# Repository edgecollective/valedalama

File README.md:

# valedalama

https://github.com/the-louie/arduino-lmic/tree/louie-add-naive-eu433-support

bossac -p /dev/cu.usbmodem14301 -e -w -v -R adafruit-circuitpython-boardname-version.bin

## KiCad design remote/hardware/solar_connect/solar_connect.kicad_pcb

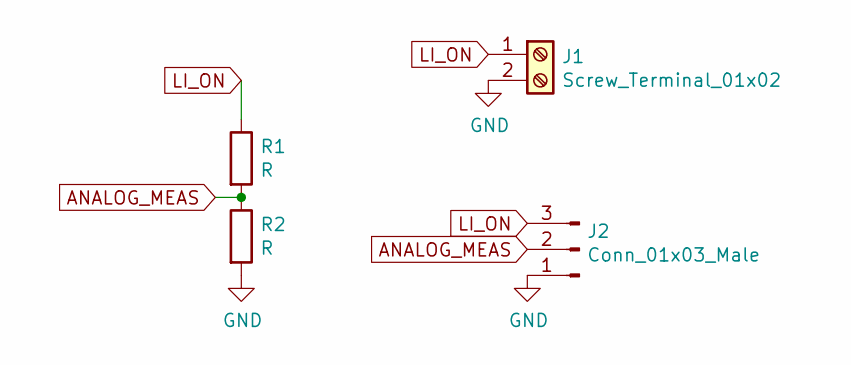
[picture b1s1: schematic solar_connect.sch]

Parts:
J1: Screw_Terminal_01x02; TerminalBlock_Phoenix_PT-1,5-2-3.5-H_1x02_P3.50mm_Horizontal
J2: Conn_01x03_Male; PinHeader_1x03_P2.54mm_Vertical
R1, R2: R; R_Axial_DIN0309_L9.0mm_D3.2mm_P2.54mm_Vertical

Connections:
ANALOG_MEAS: J2.2, R1.2, R2.1
GND: J1.2, J2.1, R2.2
LI_ON: J1.1, J2.3, R1.1

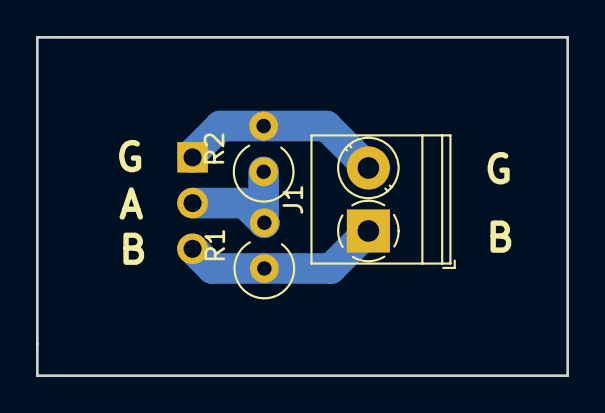
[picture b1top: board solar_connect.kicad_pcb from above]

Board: 2 copper layers, 29.5 x 18.8 mm, 4 parts (1 on the bottom side), 3 nets.

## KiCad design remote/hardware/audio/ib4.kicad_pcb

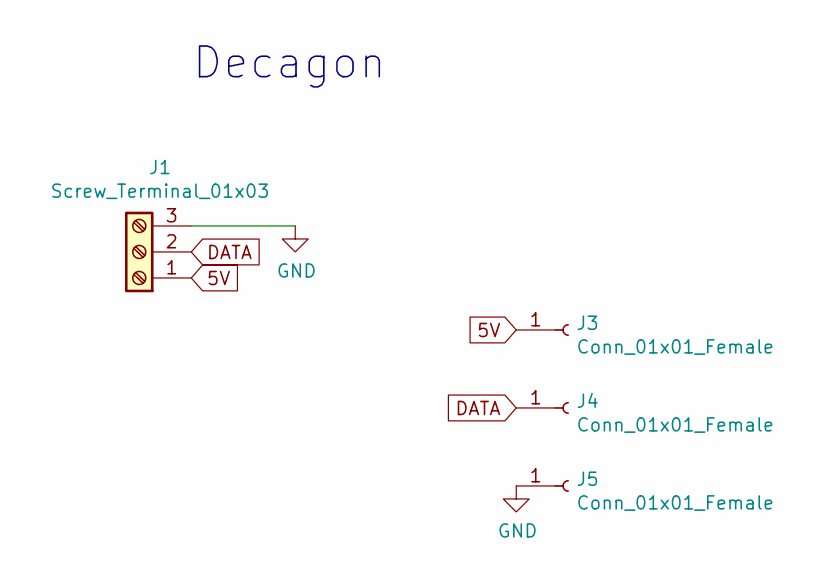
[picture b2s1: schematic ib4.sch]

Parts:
J1: Screw_Terminal_01x03; TerminalBlock_Phoenix_PT-1,5-3-3.5-H_1x03_P3.50mm_Horizontal
J3, J4, J5: Conn_01x01_Female; PinSocket_1x01_P2.54mm_Vertical

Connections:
5V: J1.1, J3.1
DATA: J1.2, J4.1
GND: J1.3, J5.1

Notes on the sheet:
Decagon

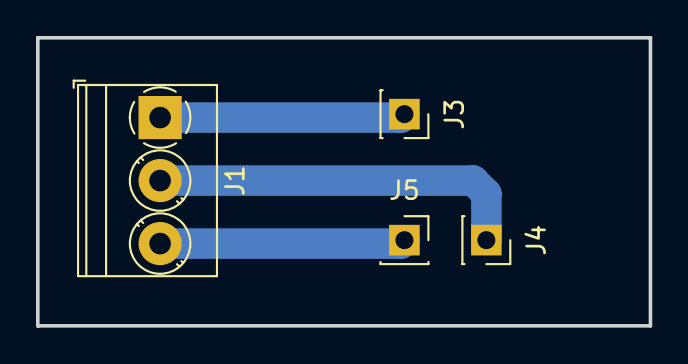
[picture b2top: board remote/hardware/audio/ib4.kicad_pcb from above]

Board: 4 copper layers, 34.0 x 16.0 mm, 4 parts (0 on the bottom side), 3 nets.

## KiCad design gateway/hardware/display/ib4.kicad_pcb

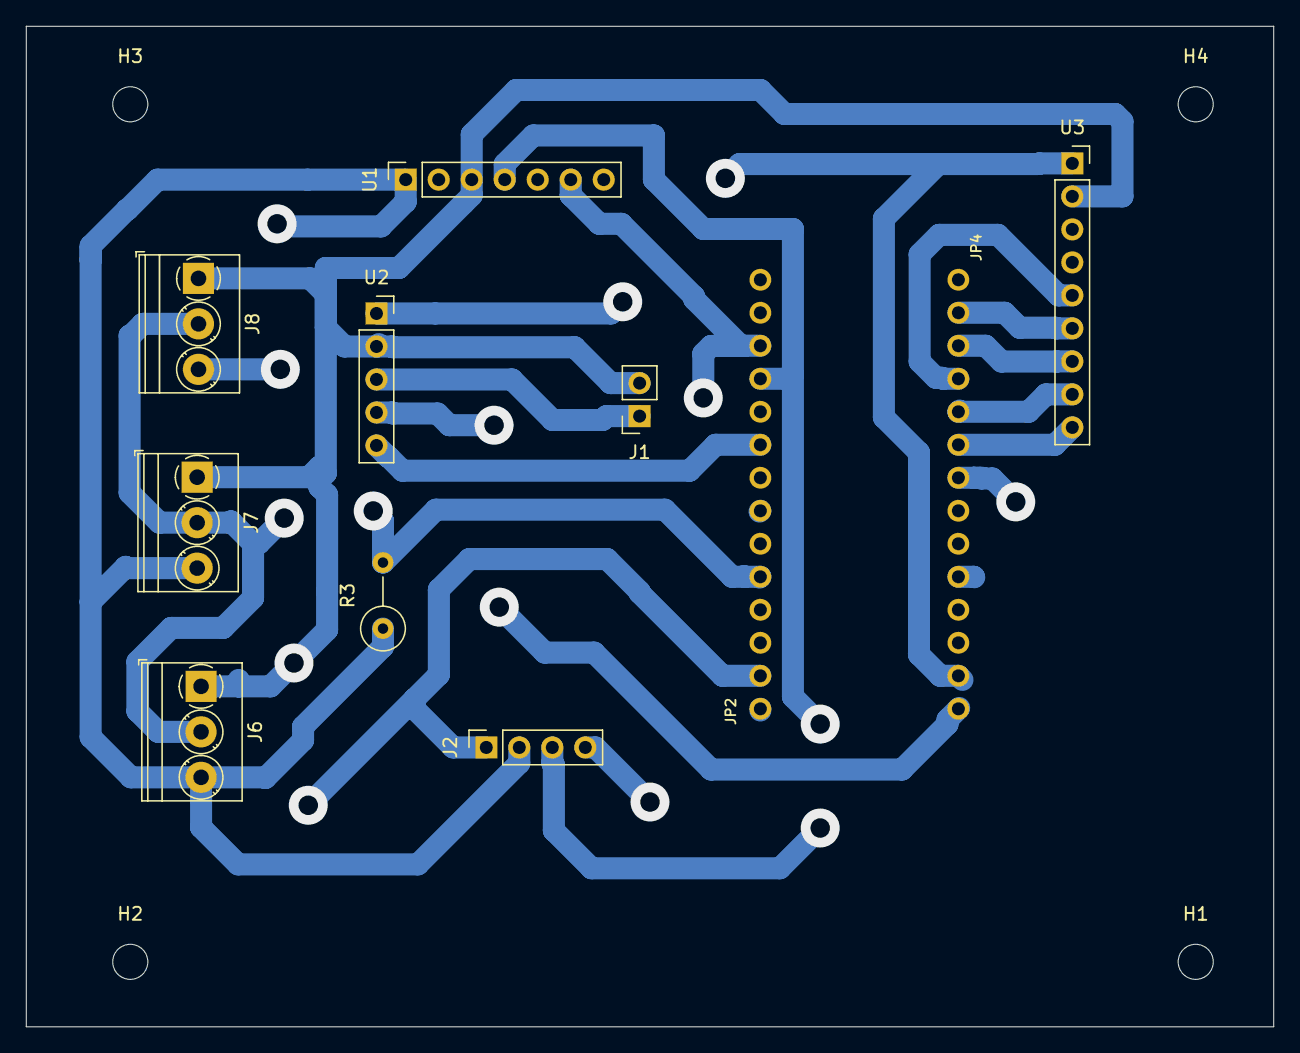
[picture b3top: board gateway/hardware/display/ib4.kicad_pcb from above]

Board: 4 copper layers, 96.0 x 77.0 mm, 15 parts (0 on the bottom side), 12 nets.

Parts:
H1, H2, H3, H4: MountingHole; MountingHole_2.7mm_M2.5
J1: Conn_01x02_Female; PinSocket_1x02_P2.54mm_Vertical
J2: Conn_01x04_Female; PinSocket_1x04_P2.54mm_Vertical
J6, J7, J8: Screw_Terminal_01x03; TerminalBlock_Phoenix_PT-1,5-3-3.5-H_1x03_P3.50mm_Horizontal
JP2, JP4: HEADER-1X14; 1X14_ROUND70
R3: R; R_Axial_DIN0309_L9.0mm_D3.2mm_P5.08mm_Vertical
U1: bme280; PinSocket_1x07_P2.54mm_Vertical
U2: tpl5110; PinSocket_1x05_P2.54mm_Vertical
U3: lora_breakout; PinSocket_1x09_P2.54mm_Vertical

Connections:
+3V3: J2.2, J6.3, J7.3, J8.3, JP4.13, R3.1, U1.1, U2.1, U3.1
D12: J6.2, J7.2, J8.2, JP2.5, R3.2
GND: J1.2, J2.1, J6.1, J7.1, J8.1, JP2.2, U1.3, U2.2, U3.2
LORA_CS: JP4.5, U3.8
LORA_RST: JP4.6, U3.9
MISO: JP4.2, U3.6
MOSI: JP4.3, U3.7
unnamed: J1.1, U2.3
SCK: JP4.4, U3.5
SCL: J2.3, JP2.11, U1.4
SDA: J2.4, JP2.12, U1.6
TIMER: JP4.14, U2.4

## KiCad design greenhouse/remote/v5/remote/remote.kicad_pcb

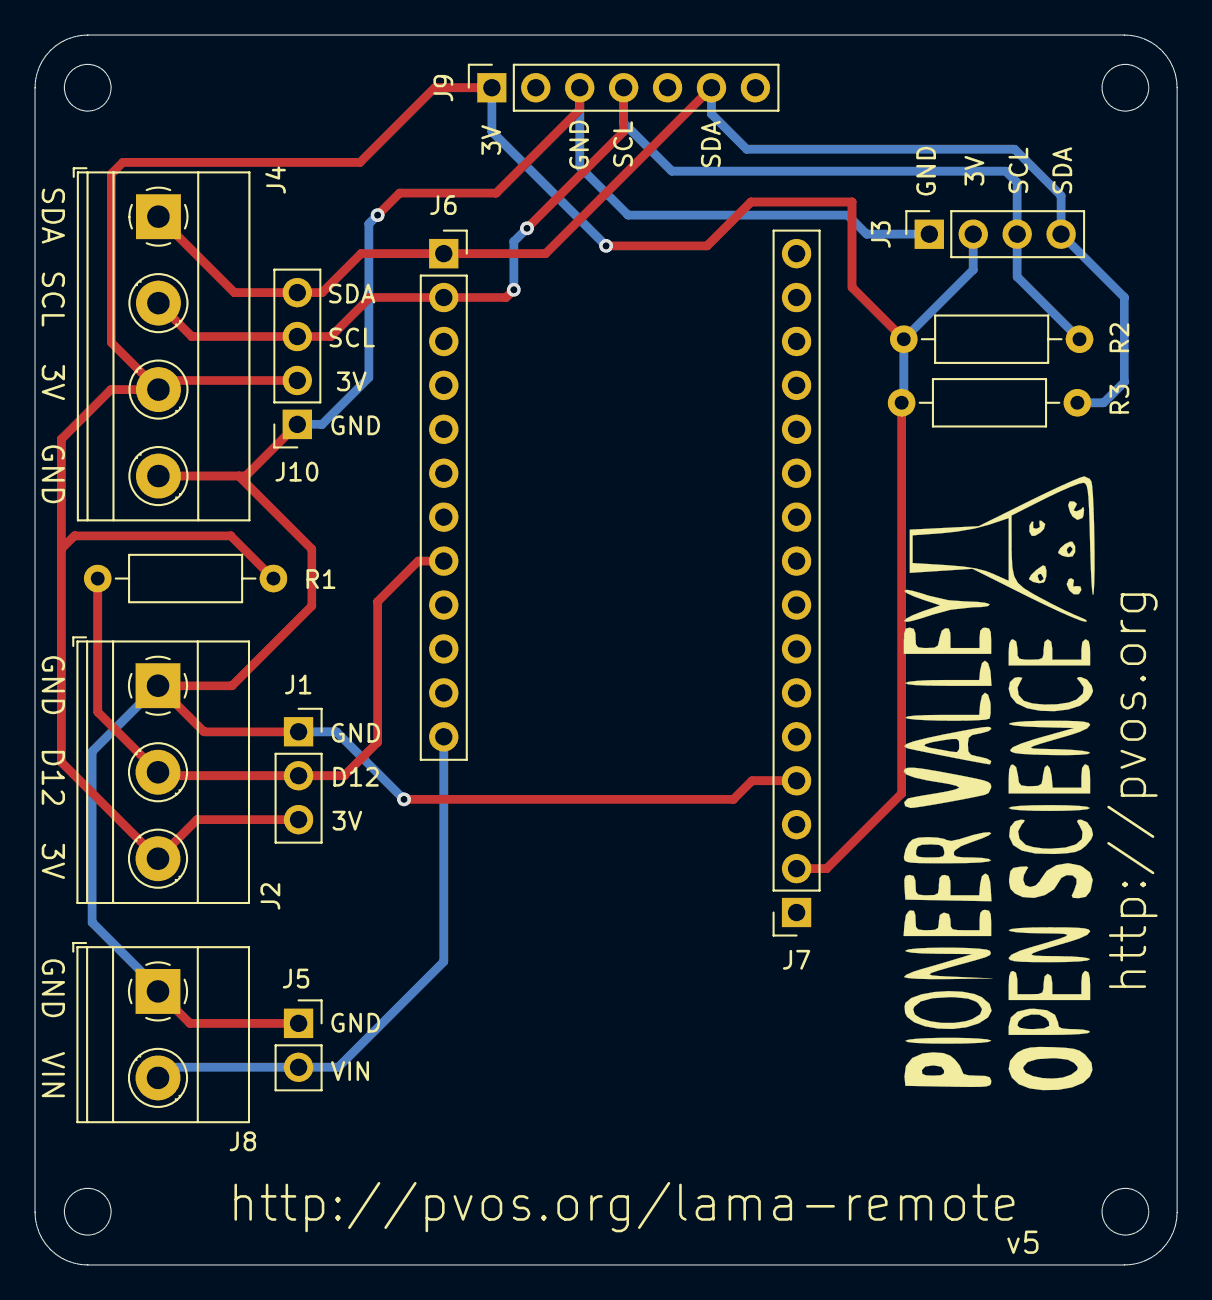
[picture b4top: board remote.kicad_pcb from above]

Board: 2 copper layers, 66.0 x 71.1 mm, 17 parts (0 on the bottom side), 6 nets.

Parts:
H1, H2, H3, H4: MountingHole; MountingHole_2.7mm_M2.5
J1: Conn_01x03_Female; PinSocket_1x03_P2.54mm_Vertical
J2: Screw_Terminal_01x03; TerminalBlock_Phoenix_MKDS-1,5-3_1x03_P5.00mm_Horizontal
J3, J10: Conn_01x04_Female; PinSocket_1x04_P2.54mm_Vertical
J4: Screw_Terminal_01x04; TerminalBlock_Phoenix_MKDS-1,5-4_1x04_P5.00mm_Horizontal
J5: Conn_01x02_Female; PinSocket_1x02_P2.54mm_Vertical
J6: Conn_01x12_Male; PinSocket_1x12_P2.54mm_Vertical
J7: Conn_01x16_Female; PinSocket_1x16_P2.54mm_Vertical
J8: Screw_Terminal_01x02; TerminalBlock_Phoenix_MKDS-1,5-2_1x02_P5.00mm_Horizontal
J9: Adafruit BME280; PinSocket_1x07_P2.54mm_Vertical
R1, R2, R3: R; R_Axial_DIN0207_L6.3mm_D2.5mm_P10.16mm_Horizontal

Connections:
+3V3: J1.3, J2.3, J3.2, J4.3, J7.2, J9.1, J10.2, R1.1, R2.1, R3.1
GND: J1.1, J2.1, J3.1, J4.4, J5.1, J7.4, J8.1, J9.3, J10.1
unnamed: J1.2, J2.2, J6.8, R1.2
unnamed: J5.2, J6.12, J8.2
SCL: J3.3, J4.2, J6.2, J9.4, J10.3, R2.2
SDA: J3.4, J4.1, J6.1, J9.6, J10.4, R3.2

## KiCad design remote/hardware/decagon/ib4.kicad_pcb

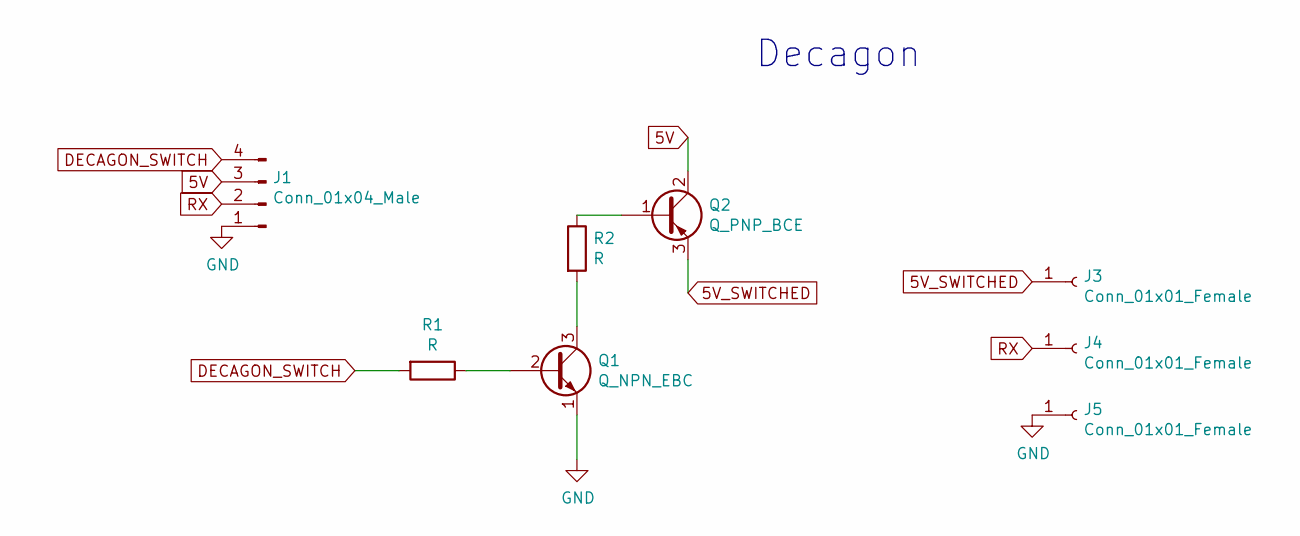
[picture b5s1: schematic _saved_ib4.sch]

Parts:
J1: Conn_01x04_Male; PinHeader_1x04_P2.54mm_Vertical
J3, J4, J5: Conn_01x01_Female; PinSocket_1x01_P2.54mm_Vertical
Q1: Q_NPN_EBC; TO-92L_Wide
Q2: Q_PNP_BCE; TO-220-3_Vertical
R1, R2: R; R_Axial_DIN0309_L9.0mm_D3.2mm_P5.08mm_Vertical

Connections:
5V: J1.3, Q2.2 (C)
5V_SWITCHED: J3.1, Q2.3 (E)
DECAGON_SWITCH: J1.4, R1.2
GND: J1.1, J5.1, Q1.1 (E)
unnamed: Q1.2 (B), R1.1
unnamed: Q1.3 (C), R2.2
unnamed: Q2.1 (B), R2.1
RX: J1.2, J4.1

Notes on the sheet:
Decagon

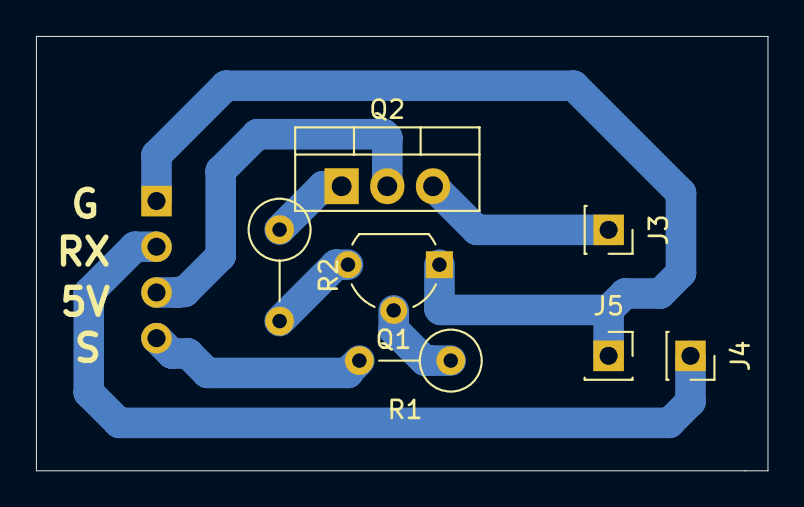
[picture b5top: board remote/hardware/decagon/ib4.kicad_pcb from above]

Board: 4 copper layers, 40.6 x 24.1 mm, 8 parts (0 on the bottom side), 8 nets.

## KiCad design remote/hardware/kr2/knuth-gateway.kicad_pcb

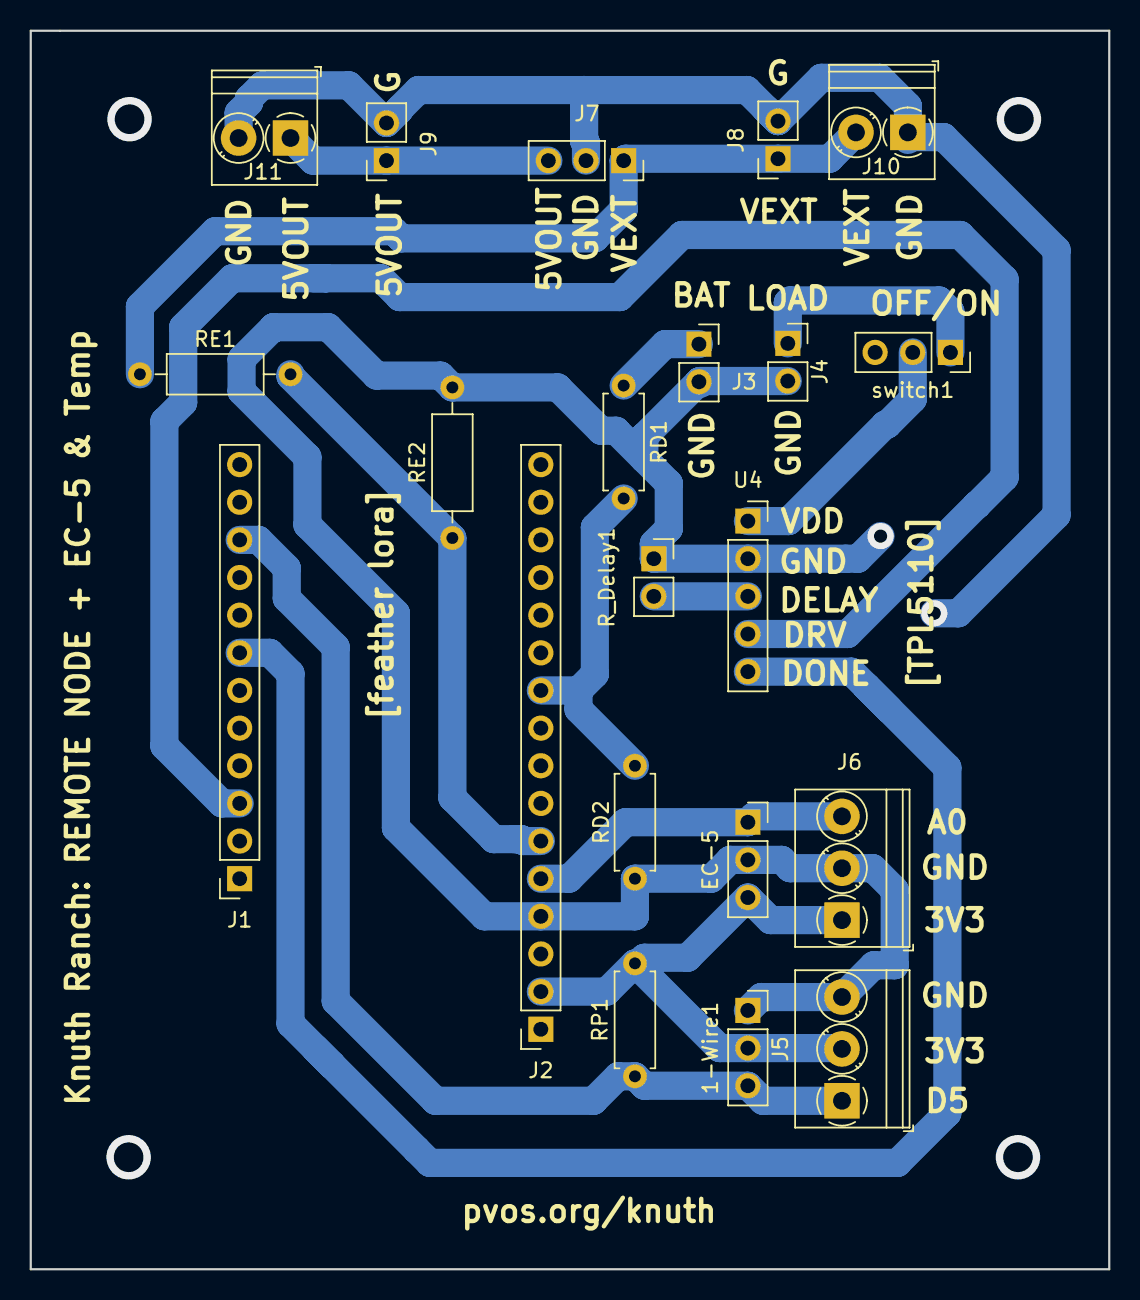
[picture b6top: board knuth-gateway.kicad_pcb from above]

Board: 2 copper layers, 72.8 x 83.6 mm, 21 parts (0 on the bottom side), 14 nets.

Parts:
1-Wire1: Conn_01x03_Female; PinSocket_1x03_P2.54mm_Vertical
EC-5: Conn_01x03_Female; PinSocket_1x03_P2.54mm_Vertical
J1: FeatherLora1; PinSocket_1x12_P2.54mm_Vertical
J2: FeatherLora2; PinSocket_1x16_P2.54mm_Vertical
J3, J4, J8, J9: Conn_01x02_Female; PinSocket_1x02_P2.54mm_Vertical
J5, J6: Screw_Terminal_01x03; TerminalBlock_Phoenix_PT-1,5-3-3.5-H_1x03_P3.50mm_Horizontal
J7: Conn_01x03_Female; PinSocket_1x03_P2.54mm_Vertical
J10, J11: Screw_Terminal_01x02; TerminalBlock_Phoenix_PT-1,5-2-3.5-H_1x02_P3.50mm_Horizontal
RD1, RD2: R; R_Axial_DIN0207_L6.3mm_D2.5mm_P7.62mm_Horizontal
RE1: R; R_Axial_DIN0207_L6.3mm_D2.5mm_P10.16mm_Horizontal
RE2: =1/14th of top R; R_Axial_DIN0207_L6.3mm_D2.5mm_P10.16mm_Horizontal
RP1: 4.7K; R_Axial_DIN0207_L6.3mm_D2.5mm_P7.62mm_Horizontal
R_Delay1: Conn_01x02_Female; PinSocket_1x02_P2.54mm_Vertical
U4: tpl5111; PinSocket_1x05_P2.54mm_Vertical
switch1: Conn_01x03_Female; PinSocket_1x03_P2.54mm_Vertical

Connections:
5V_OUT: J7.3, J9.1, J11.1
+3V3: 1-Wire1.2, EC-5.3, J2.2, J5.2, J6.1, RP1.2
A0: EC-5.1, J2.5, J6.3
A1: J2.6, RE1.2, RE2.1
A5: J2.10, RD1.2, RD2.1
BATT: J3.1, RD1.1
D5: 1-Wire1.3, J1.10, J5.1, RP1.1
D10: J1.7, U4.5
EXT_BAT: J7.1, J8.1, J10.2, RE1.1
GND: 1-Wire1.1, EC-5.2, J2.4, J3.2, J4.2, J5.3, J6.2, J7.2, J8.2, J9.2, J10.1, J11.2, RD2.2, RE2.2, R_Delay1.1, U4.2
LOAD: J4.1, switch1.1
unnamed: R_Delay1.2, U4.3
SWITCHED_LOAD: U4.1, switch1.2
VBUS: J1.3, U4.4

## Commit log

2020-11-24 re-initialize StaticJsonDocument every loop, to avoid memory leaks
